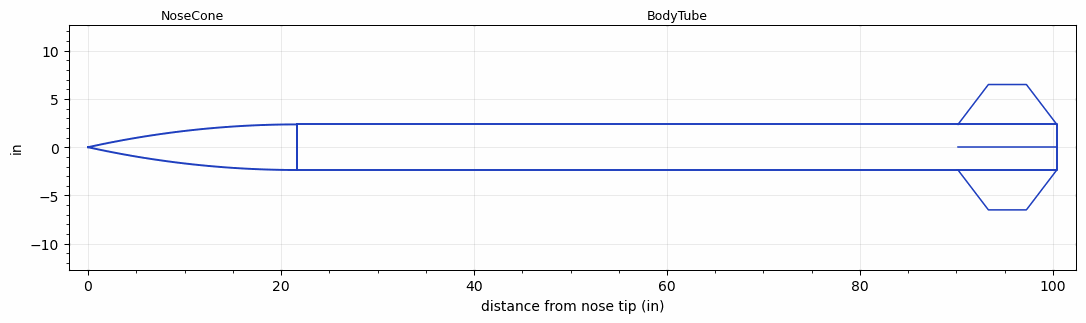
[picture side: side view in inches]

<RASAeroDocument>
 <FileVersion>2</FileVersion>
 <RocketDesign>
  <NoseCone>
   <Length>21.6535</Length>
   <Diameter>4.7244</Diameter>
   <Shape>Tangent Ogive</Shape>
   <Location>0</Location>
  </NoseCone>
  <BodyTube>
   <Length>78.74</Length>
   <Diameter>4.7244</Diameter>
   <Location>21.6535</Location>
   <Fin>
    <Count>4</Count>
    <Chord>10.2362</Chord>
    <Span>4.1338</Span>
    <SweepDistance>3.1496</SweepDistance>
    <TipChord>3.937</TipChord>
    <Thickness>0.1378</Thickness>
    <Location>10.2362</Location>
    <AirfoilSection>Rounded</AirfoilSection>
   </Fin>
  </BodyTube>
  <Surface>Smooth Paint</Surface>
  <ModifiedBarrowman>False</ModifiedBarrowman>
  <Turbulence>False</Turbulence>
  <UseBooster1>False</UseBooster1>
  <UseBooster2>False</UseBooster2>
 </RocketDesign>
 <LaunchSite>
  <Altitude>0</Altitude>
  <Pressure>29.9214</Pressure>
  <RodAngle>0</RodAngle>
  <RodLength>3.2808</RodLength>
  <Temperature>59</Temperature>
  <WindSpeed>4.4739</WindSpeed>
 </LaunchSite>
 <Recovery>
  <Altitude1>0</Altitude1>
  <Altitude2>0</Altitude2>
  <DeviceType1>None</DeviceType1>
  <DeviceType2>None</DeviceType2>
  <Event1>False</Event1>
  <Event2>False</Event2>
  <Size1>0</Size1>
  <Size2>0</Size2>
  <EventType1>None</EventType1>
  <EventType2>None</EventType2>
  <CD1>0</CD1>
  <CD2>0</CD2>
 </Recovery>
 <SimulationList>
  <Simulation>
   <SustainerEngine>M685W-PS  (AT)</SustainerEngine>
   <SustainerLaunchWt>42.4</SustainerLaunchWt>
   <SustainerCG>70.7</SustainerCG>
   <SustainerIgnitionDelay>0</SustainerIgnitionDelay>
   <Booster1SeparationDelay>0</Booster1SeparationDelay>
   <Booster1IgnitionDelay>0</Booster1IgnitionDelay>
   <IncludeBooster1>False</IncludeBooster1>
   <Booster2Delay>0</Booster2Delay>
   <IncludeBooster2>False</IncludeBooster2>
  </Simulation>
 </SimulationList>
</RASAeroDocument>
